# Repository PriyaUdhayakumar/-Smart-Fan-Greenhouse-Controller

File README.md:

# Smart Fan and Greenhouse Controller using ESP32

## Project Overview

An ESP32-based embedded systems project developed using ESP-IDF and Embedded C. The system monitors temperature using an LM75 digital temperature sensor and uses a potentiometer to adjust the target temperature.

The firmware implements temperature-based fan control using PWM, LED status indication, GPIO interrupt handling for manual control, and UART messages for debugging.

## Features

- Temperature monitoring using the LM75 sensor over I²C.
- Adjustable temperature setpoint using an ADC input.
- PWM-based fan speed control.
- Three status LEDs for operating-condition indication.
- GPIO interrupt-based button input.
- UART output for debugging and status monitoring.
- FreeRTOS-based application execution using ESP-IDF.

## Hardware Components

| Component | Purpose |
|---|---|
| ESP32 | Main microcontroller |
| LM75 | Digital temperature sensor |
| Potentiometer | Temperature setpoint adjustment |
| DC fan | Temperature regulation |
| Three LEDs | Status indication |
| Push button | Manual control input |

## Pin Configuration

| Function | ESP32 GPIO / Setting |
|---|---|
| Green LED | GPIO 4 |
| Yellow LED | GPIO 16 |
| Red LED | GPIO 17 |
| Fan PWM | GPIO 18 |
| Button input | GPIO 34 |
| I²C SDA | GPIO 21 |
| I²C SCL | GPIO 22 |
| LM75 I²C address | 0x48 |
| ADC input | ADC1 Channel 0 |
| PWM frequency | 1 kHz |
| PWM resolution | 10-bit |
| UART baud rate | 115200 |

**Note:** Confirm the GPIO mapping against your exact ESP32 variant. On the original ESP32, ADC1 Channel 0 maps to GPIO 36, and GPIO 34 requires external button biasing because it has no internal pull-up or pull-down.

## Working Principle

### 1. Temperature Measurement
The ESP32 communicates with the LM75 temperature sensor through the I²C interface and reads the temperature register.

### 2. Temperature Setpoint
The potentiometer provides an analog voltage to the ADC. The firmware maps the ADC reading to a target temperature range of approximately 20°C to 40°C.

### 3. Fan Control
The firmware compares the measured temperature with the target temperature and selects a PWM duty level.

| Temperature condition | Intended fan duty |
|---|---:|
| At or below target | 0% |
| Above target by less than 2°C | 30% |
| 2°C to less than 5°C above target | 60% |
| 5°C or more above target | 100% |

The manual button and automatic temperature-control logic require further refinement to ensure that manual operation behaves consistently.

### 4. LED Status Indication
Three LEDs indicate the temperature and fan operating conditions.

### 5. UART Monitoring
UART messages provide status information for debugging and monitoring the control logic.

## Software and Tools

- ESP-IDF
- Embedded C
- FreeRTOS
- GPIO driver
- ADC one-shot driver
- LEDC PWM driver
- I²C master driver
- UART driver

## Learning Outcomes

- Embedded C programming with ESP-IDF.
- I²C sensor interfacing.
- ADC-based analog input processing.
- PWM configuration and actuator control.
- GPIO interrupt handling.
- UART-based debugging.
- Integration of sensors and peripheral drivers.

## Project Status

The main firmware implementation has been drafted. Code review, manual-control refinements, error handling, and hardware validation remain pending.

## Future Improvements

- Organize firmware into reusable source and header files.
- Add button debounce and robust sensor-error handling.
- Refine manual and automatic operating modes.
- Improve temperature-control stability.
- Add hardware test results and demonstration images.

## Author

**Priya Udhayakumar**

Embedded Systems and PCB Design

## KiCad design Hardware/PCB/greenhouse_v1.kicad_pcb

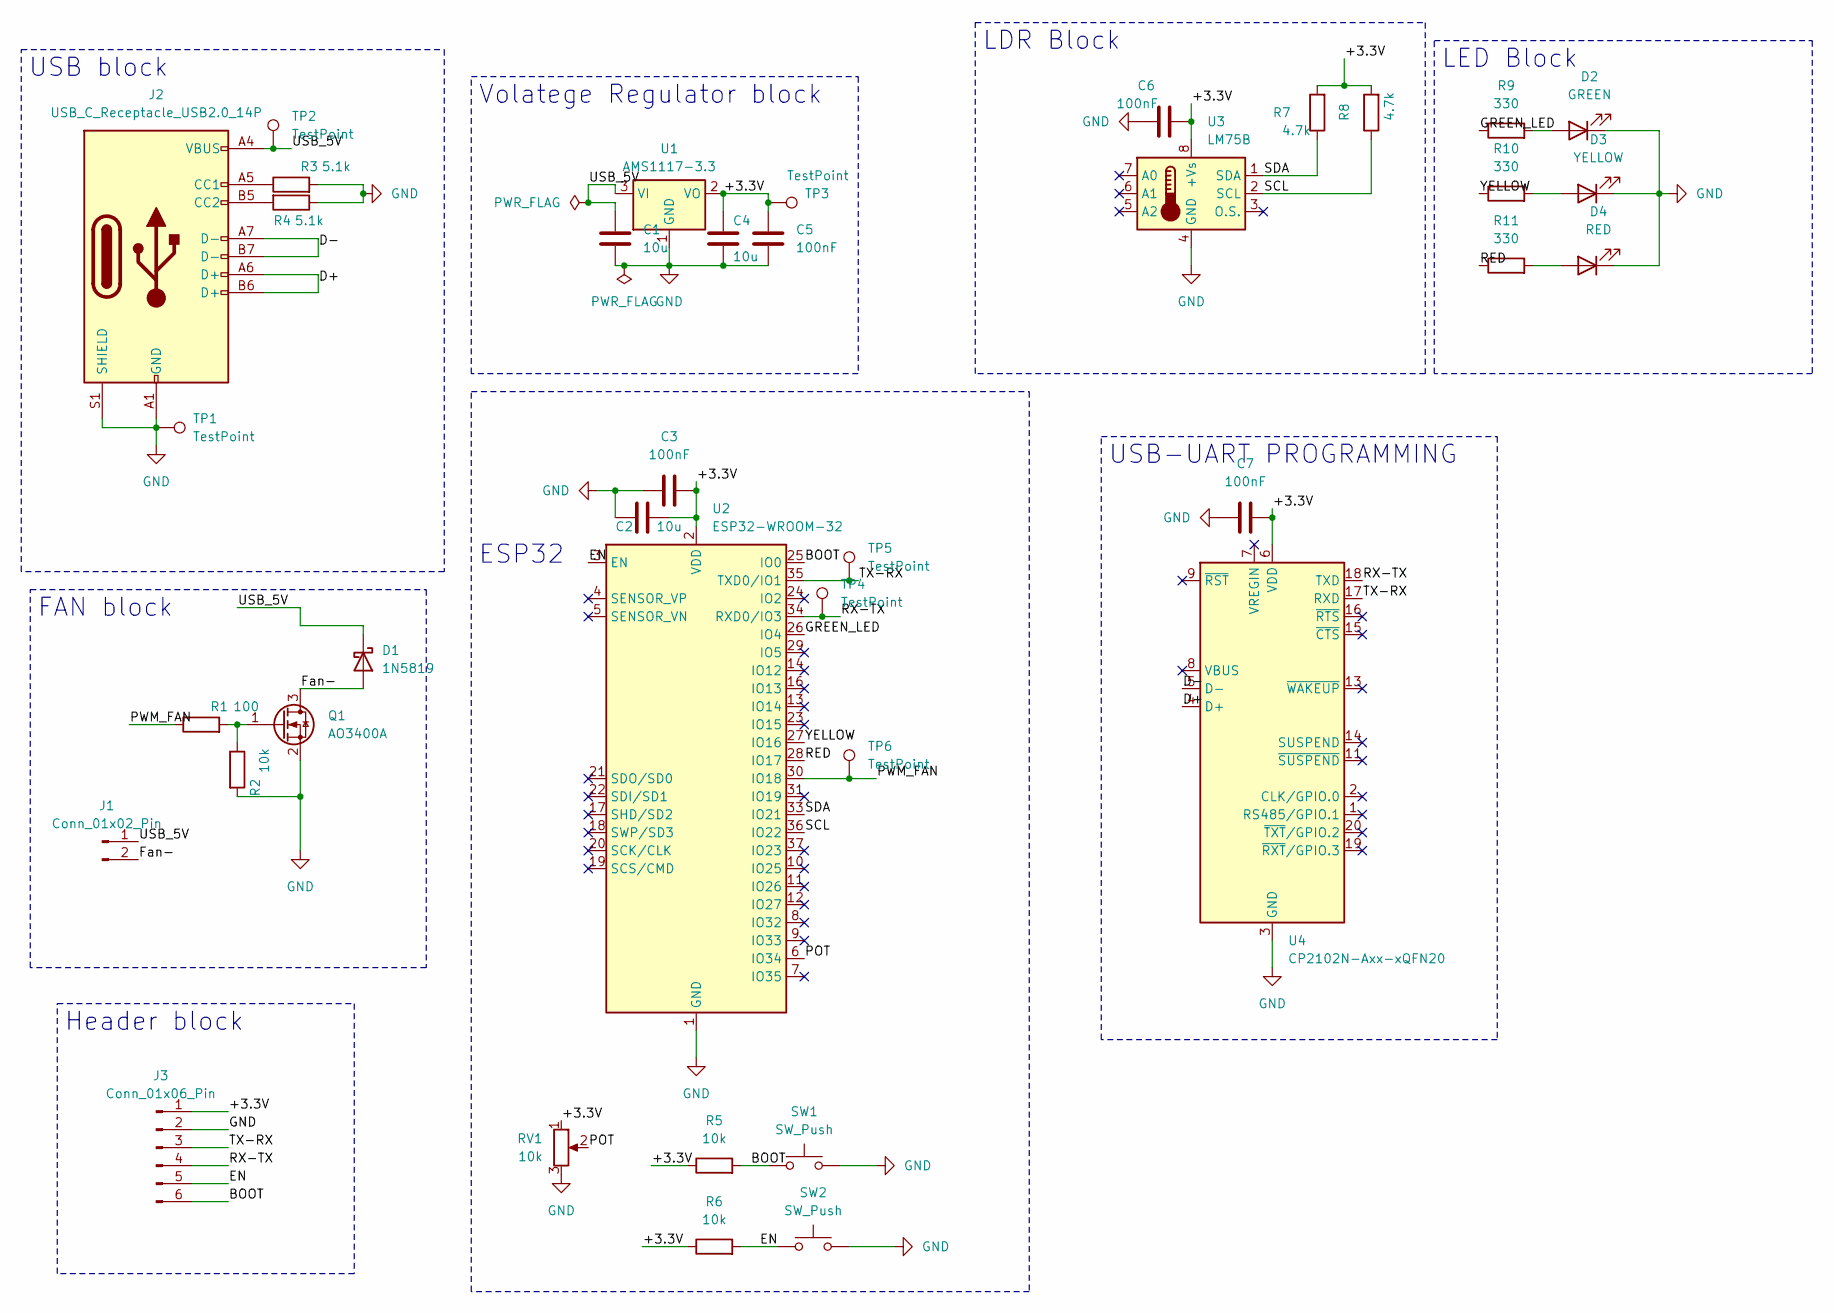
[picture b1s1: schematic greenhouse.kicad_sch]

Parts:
C1, C2, C4: 10u; C_0805_2012Metric
C3, C5, C6, C7: 100nF; C_0805_2012Metric
D1: 1N5819; D_DO-41_SOD81_P10.16mm_Horizontal
D2: GREEN; LED_0805_2012Metric
D3: YELLOW; LED_0805_2012Metric
D4: RED; LED_0805_2012Metric
J1: Conn_01x02_Pin; PinHeader_1x02_P2.54mm_Horizontal
J2: USB_C_Receptacle_USB2.0_14P; USB_C_Receptacle_GCT_USB4105-xx-A_16P_TopMnt_Horizontal
J3: Conn_01x06_Pin; PinHeader_1x06_P2.54mm_Horizontal
Q1: AO3400A; SOT-23
R1: 100; R_0805_2012Metric
R2, R5, R6: 10k; R_0805_2012Metric
R3, R4: 5.1k; R_0805_2012Metric
R7, R8: 4.7k; R_0805_2012Metric
R9, R10, R11: 330; R_0805_2012Metric
RV1: 10k; Potentiometer_Bourns_3296W_Vertical
SW1, SW2: SW_Push; SW_SPST_TL3342
TP1, TP2, TP3, TP4, TP5, TP6: TestPoint; TestPoint_Pad_D2.0mm
U1: AMS1117-3.3; SOT-223-3_TabPin2
U2: ESP32-WROOM-32
U3: LM75B; SOIC-8_3.9x4.9mm_P1.27mm
U4: CP2102N-Axx-xQFN20; SiliconLabs_QFN-20-1EP_3x3mm_P0.5mm_EP1.8x1.8mm

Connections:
/+3.3V: C2.2, C3.2, C4.1, C5.2, C6.2, C7.2, J3.1, R5.1, R6.1, R7.2, R8.2, RV1.1, TP3.1, U1.2 (VO), U2.2 (VDD), U3.8 (+Vs), U4.6 (VDD)
/BOOT: J3.6, R5.2, SW1.1, U2.25 (IO0)
/D+: J2.A6 (D+), J2.B6 (D+), U4.4 (D+)
/D-: J2.A7 (D-), J2.B7 (D-), U4.5 (D-)
/EN: J3.5, R6.2, SW2.1, U2.3 (EN)
/Fan-: D1.2 (A), J1.2, Q1.3 (D)
/GREEN_LED: R9.1, U2.26 (IO4)
/POT: RV1.2, U2.6 (IO34)
/PWM_FAN: R1.1, TP6.1, U2.30 (IO18)
/RED: R11.1, U2.28 (IO17)
/RX-TX: J3.4, TP4.1, U2.34 (RXD0/IO3), U4.18 (TXD)
/SCL: R8.1, U2.36 (IO22), U3.2 (SCL)
/SDA: R7.1, U2.33 (IO21), U3.1 (SDA)
/TX-RX: J3.3, TP5.1, U2.35 (TXD0/IO1), U4.17 (RXD)
/USB_5V: C1.1, D1.1 (K), J1.1, J2.A4 (VBUS), J2.A9 (VBUS), J2.B4 (VBUS), J2.B9 (VBUS), TP2.1, U1.3 (VI)
/YELLOW: R10.1, U2.27 (IO16)
GND: C1.2, C2.1, C3.1, C4.2, C5.1, C6.1, C7.1, D2.1 (K), D3.1 (K), D4.1 (K), J2.A1 (GND), J2.A12 (GND), J2.B1 (GND), J2.B12 (GND), J2.S1 (SHIELD), J3.2, Q1.2 (S), R2.2, R3.2, R4.1, RV1.3, SW1.2, SW2.2, TP1.1, U1.1 (GND), U2.1 (GND), U2.15 (GND), U2.38 (GND), U2.39 (GND), U3.4 (GND), U4.3 (GND), U4.12 (GND), U4.21 (GND)
unnamed: D2.2 (A), R9.2
unnamed: D3.2 (A), R10.2
unnamed: D4.2 (A), R11.2
unnamed: J2.A5 (CC1), R3.1
unnamed: J2.B5 (CC2), R4.2
unnamed: Q1.1 (G), R1.2, R2.1

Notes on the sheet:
LDR Block
Volatege Regulator block
FAN block
ESP32
USB block
LED Block
Header block
USB-UART PROGRAMMING

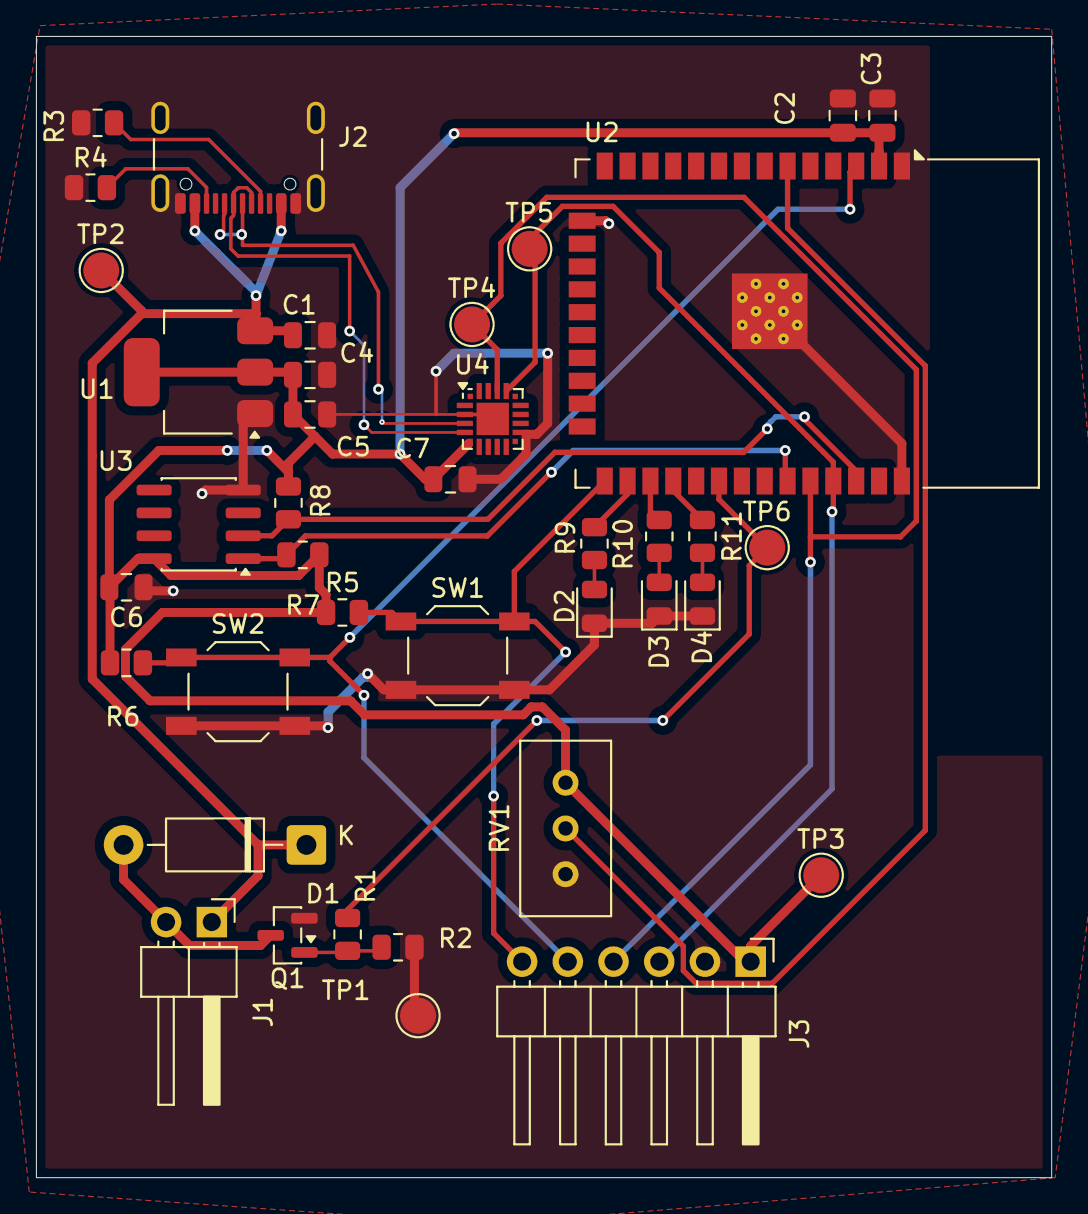
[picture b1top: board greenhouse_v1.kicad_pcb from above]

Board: 2 copper layers, 56.4 x 63.4 mm, 39 parts (0 on the bottom side), 23 nets.
